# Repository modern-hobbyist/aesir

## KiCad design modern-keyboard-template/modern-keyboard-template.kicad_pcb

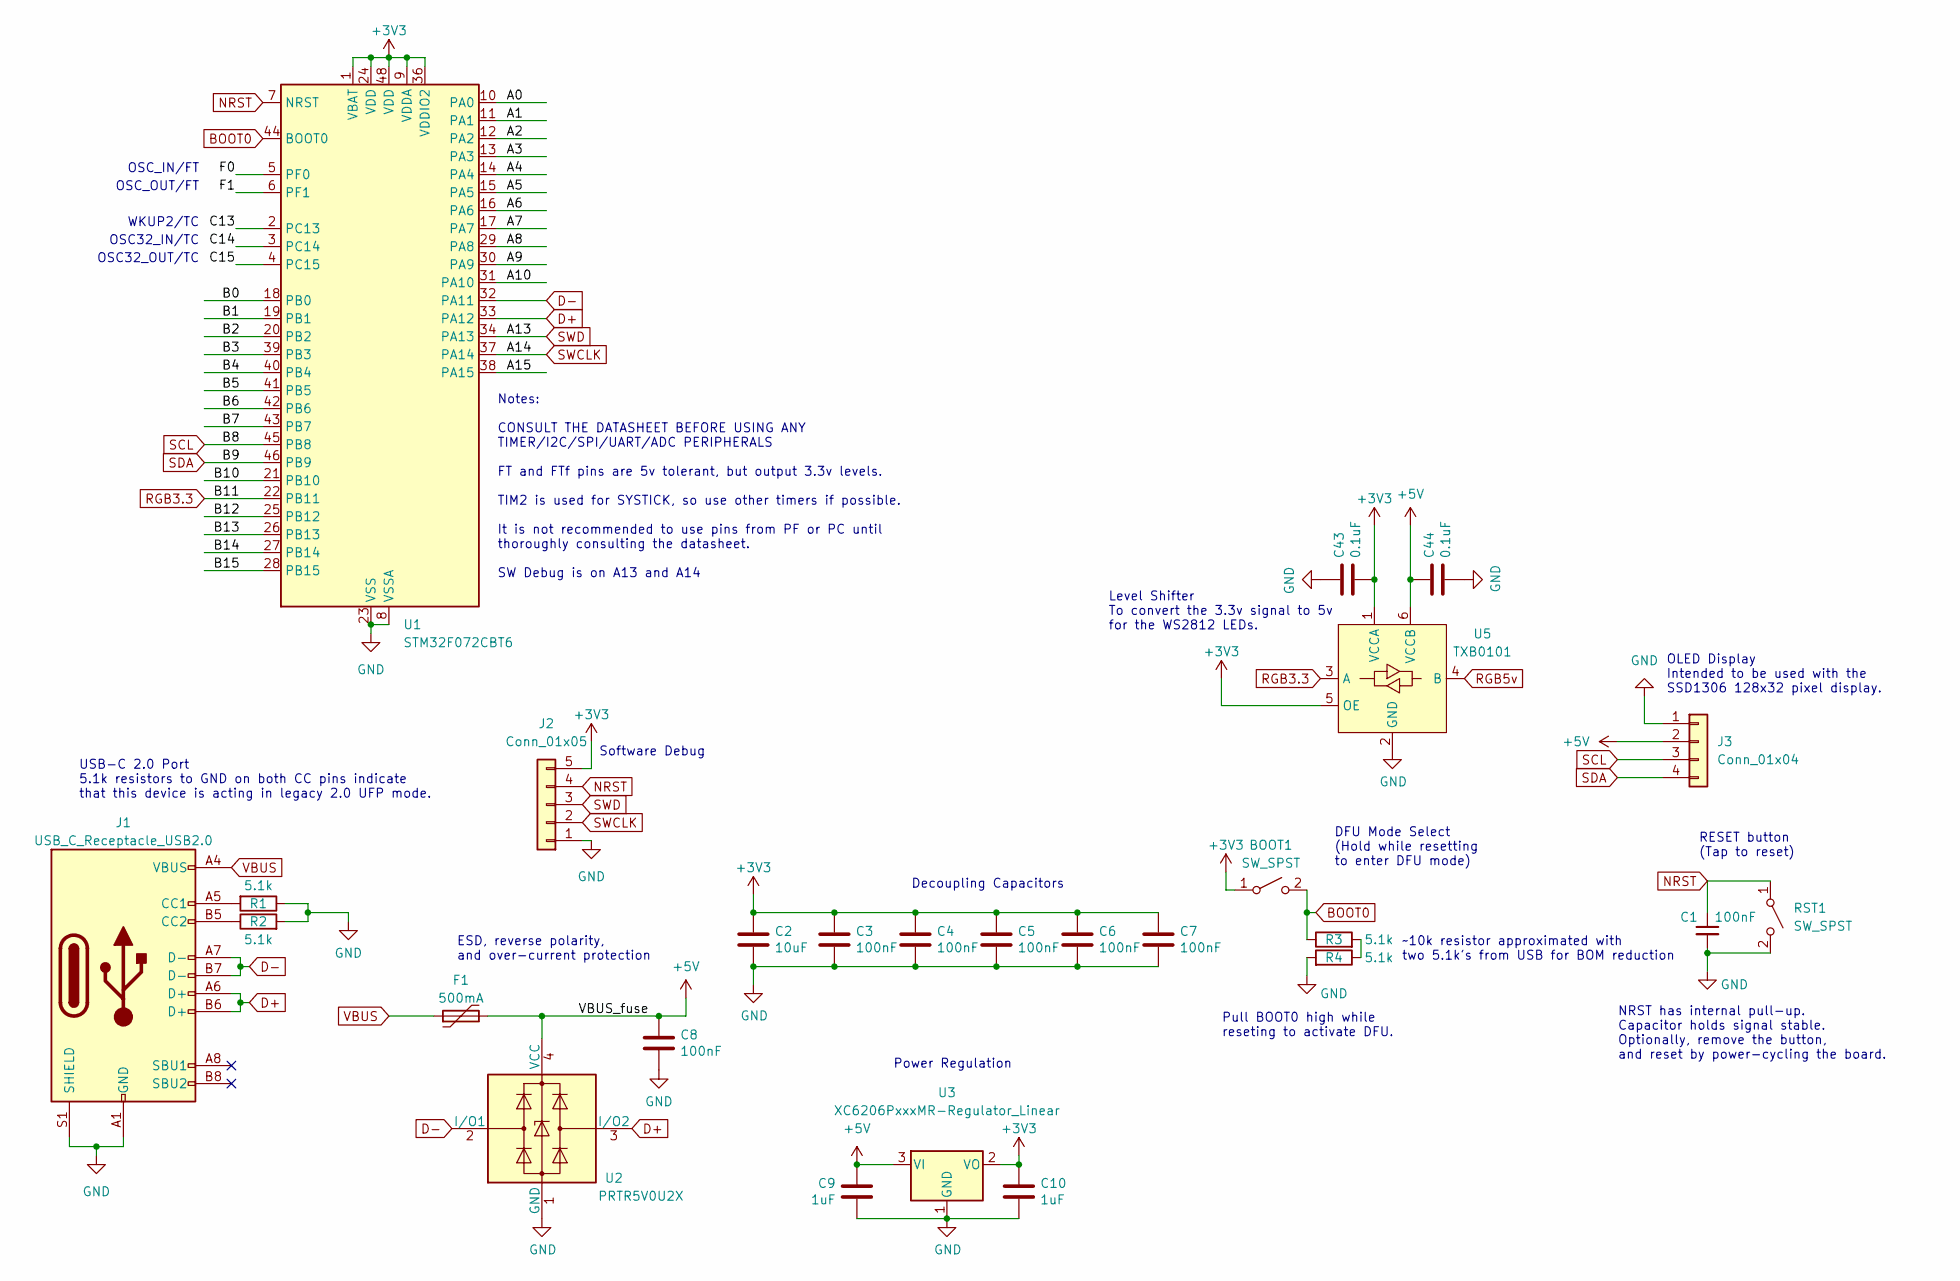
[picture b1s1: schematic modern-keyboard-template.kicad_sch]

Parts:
BOOT1: SW_SPST; SW_SPST_TL3342
C1, C3, C4, C5, C6, C7, C8: 100nF; C_0402_1005Metric; LCSC C307331
C2: 10uF; C_0603_1608Metric; LCSC C307331
C9, C10: 1uF; C_0402_1005Metric; LCSC C307331
C43, C44: 0.1uF; C_0402_1005Metric; LCSC C307331
F1: 500mA; Fuse_1206_3216Metric; LCSC C135341
J1: USB_C_Receptacle_USB2.0; USB_C_Receptacle_HRO_TYPE-C-31-M-12; JlcRotOffset 180
J2: Conn_01x05; PinHeader_1x05_P2.54mm_Vertical
J3: Conn_01x04; SSD1306-0.91-OLED-4pin-128x32
R1, R2, R3, R4: 5.1k; R_0402_1005Metric
RST1: SW_SPST; SW_SPST_TL3342
U1: STM32F072CBT6; LQFP-48_7x7mm_P0.5mm; JlcRotOffset 90
U2: PRTR5V0U2X; SOT-143; LCSC C2827688
U3: XC6206PxxxMR-Regulator_Linear; SOT-23; LCSC C5446
U5: TXB0101; SOT-363_SC-70-6_Handsoldering; LCSC C324081

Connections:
+3V3: BOOT1.1 (A), C2.1, C3.1, C4.1, C5.1, C6.1, C7.1, C10.1, C43.2, J2.5, U1.1 (VBAT), U1.9 (VDDA), U1.24 (VDD), U1.36 (VDDIO2), U1.48 (VDD), U3.2 (VO), U5.1 (VCCA), U5.5 (OE)
+5V: C8.1, C9.1, C44.1, F1.2, J3.2, U2.4 (VCC), U3.3 (VI), U5.6 (VCCB)
/A0: U1.10 (PA0)
/A1: U1.11 (PA1)
/A2: U1.12 (PA2)
/A3: U1.13 (PA3)
/A4: U1.14 (PA4)
/A5: U1.15 (PA5)
/A6: U1.16 (PA6)
/A7: U1.17 (PA7)
/A8: U1.29 (PA8)
/A9: U1.30 (PA9)
/A10: U1.31 (PA10)
/A15: U1.38 (PA15)
/B0: U1.18 (PB0)
/B1: U1.19 (PB1)
/B2: U1.20 (PB2)
/B3: U1.39 (PB3)
/B4: U1.40 (PB4)
/B5: U1.41 (PB5)
/B6: U1.42 (PB6)
/B7: U1.43 (PB7)
/B10: U1.21 (PB10)
/B12: U1.25 (PB12)
/B13: U1.26 (PB13)
/B14: U1.27 (PB14)
/B15: U1.28 (PB15)
/C13: U1.2 (PC13)
/C14: U1.3 (PC14)
/C15: U1.4 (PC15)
/F0: U1.5 (PF0)
/F1: U1.6 (PF1)
BOOT0: BOOT1.2 (B), R3.1, U1.44 (BOOT0)
D+: J1.A6 (D+), J1.B6 (D+), U1.33 (PA12), U2.3 (I/O2)
D-: J1.A7 (D-), J1.B7 (D-), U1.32 (PA11), U2.2 (I/O1)
GND: C1.2, C2.2, C3.2, C4.2, C5.2, C6.2, C7.2, C8.2, C9.2, C10.2, C43.1, C44.2, J1.A1 (GND), J1.A12 (GND), J1.B1 (GND), J1.B12 (GND), J1.S1 (SHIELD), J2.1, J3.1, R1.1, R2.2, R4.2, RST1.2 (B), U1.8 (VSSA), U1.23 (VSS), U1.35 (VSS), U1.47 (VSS), U2.1 (GND), U3.1 (GND), U5.2 (GND)
NRST: C1.1, J2.4, RST1.1 (A), U1.7 (NRST)
unnamed: J1.A5 (CC1), R1.2
unnamed: J1.B5 (CC2), R2.1
unnamed: R3.2, R4.1
RGB3.3: U1.22 (PB11), U5.3 (A)
RGB5v: U5.4 (B)
SCL: J3.3, U1.45 (PB8)
SDA: J3.4, U1.46 (PB9)
SWCLK: J2.2, U1.37 (PA14)
SWD: J2.3, U1.34 (PA13)
VBUS: F1.1, J1.A4 (VBUS), J1.A9 (VBUS), J1.B4 (VBUS), J1.B9 (VBUS)

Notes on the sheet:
Decoupling Capacitors
~10k resistor approximated with two 5.1k's from USB for BOM reduction
Notes: CONSULT THE DATASHEET BEFORE USING ANY TIMER/I2C/SPI/UART/ADC PERIPHERALS FT and FTf pins are 5v tolerant, but output 3.3v levels. TIM2 is used for SYSTICK, so use other timers if possible. It is not recommended to use pins from PF or PC until thoroughly consulting the datasheet. SW Debug is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
RESET button (Tap to reset)
Power Regulation
OSC_IN/FT
OLED Display Intended to be used with the SSD1306 128x32 pixel display.
OSC32_OUT/TC
USB-C 2.0 Port 5.1k resistors to GND on both CC pins indicate that this device is acting in legacy 2.0 UFP mode.
WKUP2/TC
OSC_OUT/FT
ESD, reverse polarity, and over-current protection
Software Debug
NRST has internal pull-up. Capacitor holds signal stable. Optionally, remove the button, and reset by power-cycling the board.
OSC32_IN/TC
Pull BOOT0 high while reseting to activate DFU.
Level Shifter To convert the 3.3v signal to 5v for the WS2812 LEDs.
DFU Mode Select (Hold while resetting to enter DFU mode)

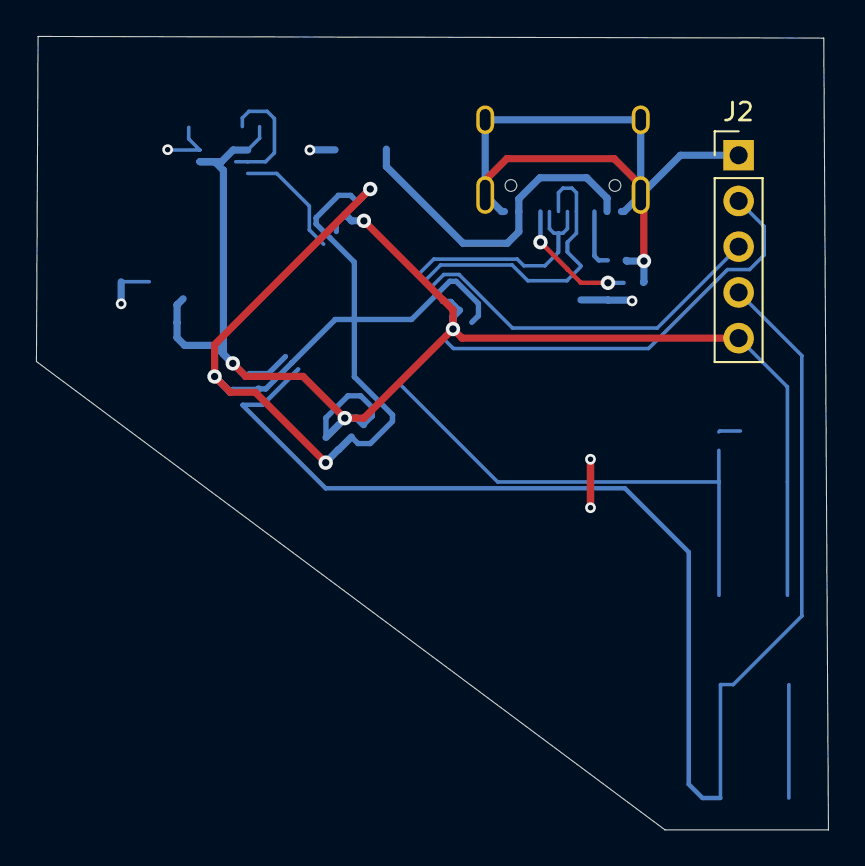
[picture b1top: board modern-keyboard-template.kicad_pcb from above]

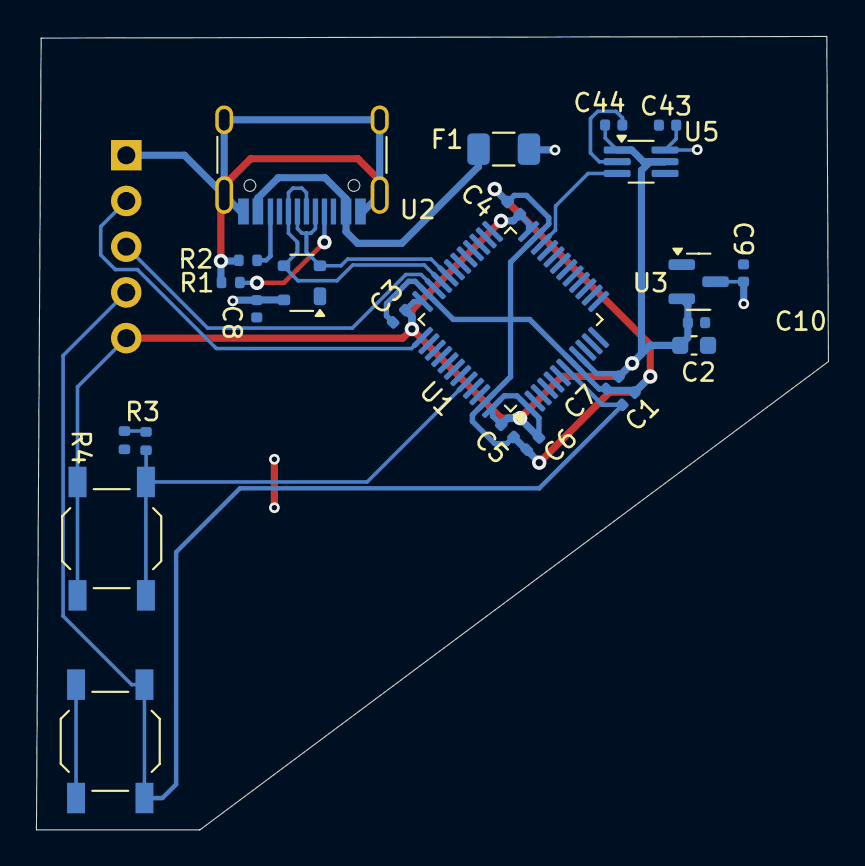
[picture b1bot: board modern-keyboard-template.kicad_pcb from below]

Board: 2 copper layers, 44.0 x 44.1 mm, 25 parts (24 on the bottom side), 14 nets.

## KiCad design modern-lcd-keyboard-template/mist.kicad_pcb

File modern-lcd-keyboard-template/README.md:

# Modern LCD Keyboard Template

> **Note:** This PCB is untested. I made updates to this design to address issues I had with the previous version, but I haven't ordered boards, nor have I written the matching firmware for it.

This is a starter template for a Keyboard PCB to help you get started quickly with the right footprints and supplemental components to get it done right.

## Features
- TBD

## Specifications

- **Microcontroller**: STM32G474CETx
- **Key Layout**: Split layout with additional keys for layers and macros.
- **Display**: 2.2" LCD (320x240 resolution) per half.
- **Lighting**: SK6812 Mini RGB LEDs.
- **Switches**: Kailh Choc Low Profile.

## License

This project is licensed under the MIT License. See the [LICENSE](../LICENSE) file for details.

## Acknowledgments

- The QMK community for their amazing firmware.
- Adafruit for the GFX library support.
- Inspiration from the mechanical keyboard enthusiast community.

---

For more information, check out the [Modern Hobbyist YouTube channel](https://www.youtube.com/ModernHobbyist) for videos about this project!

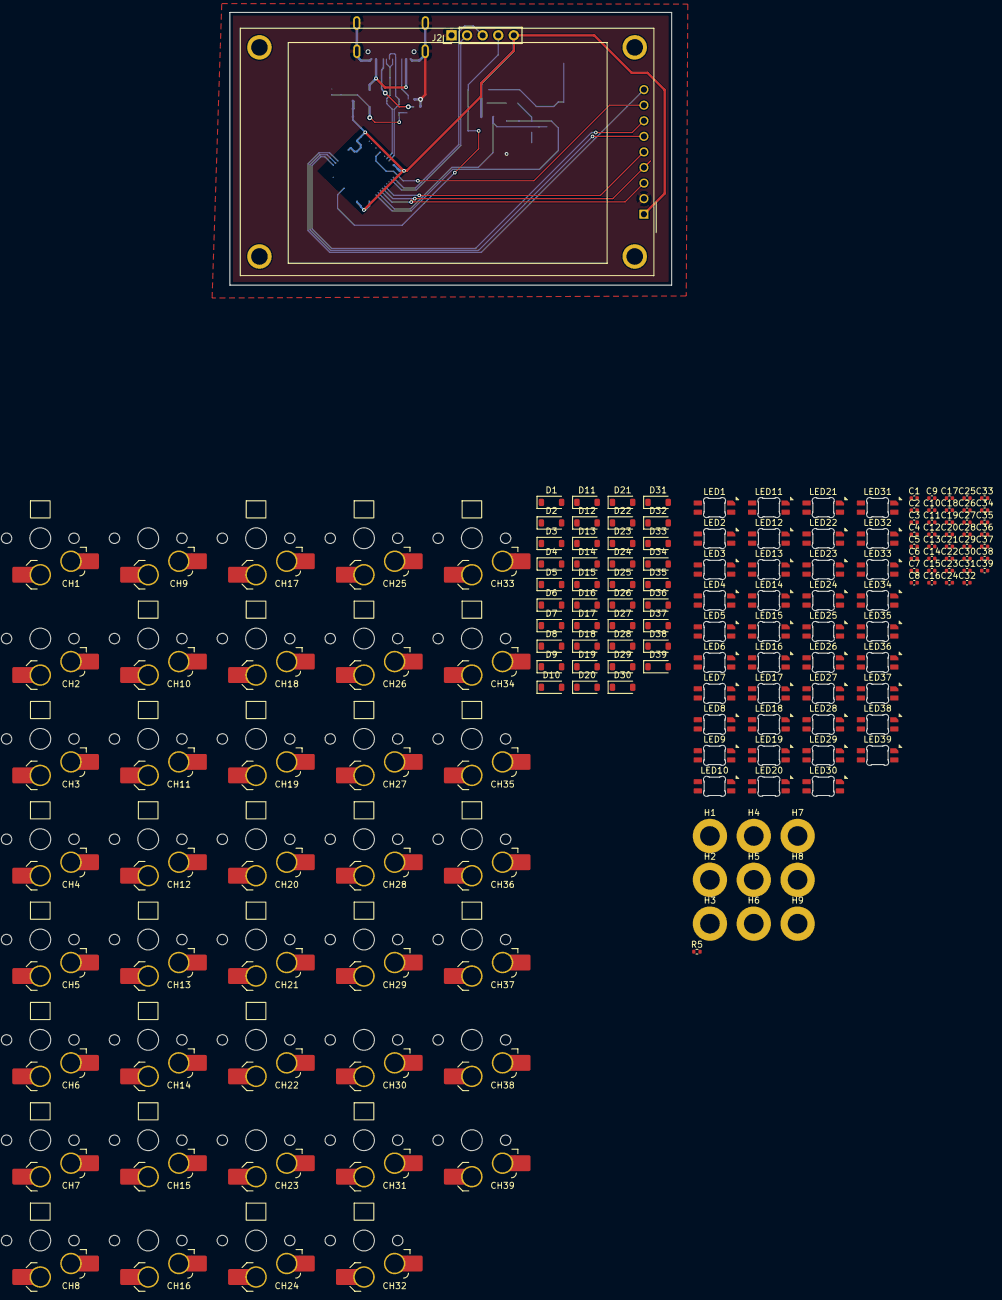
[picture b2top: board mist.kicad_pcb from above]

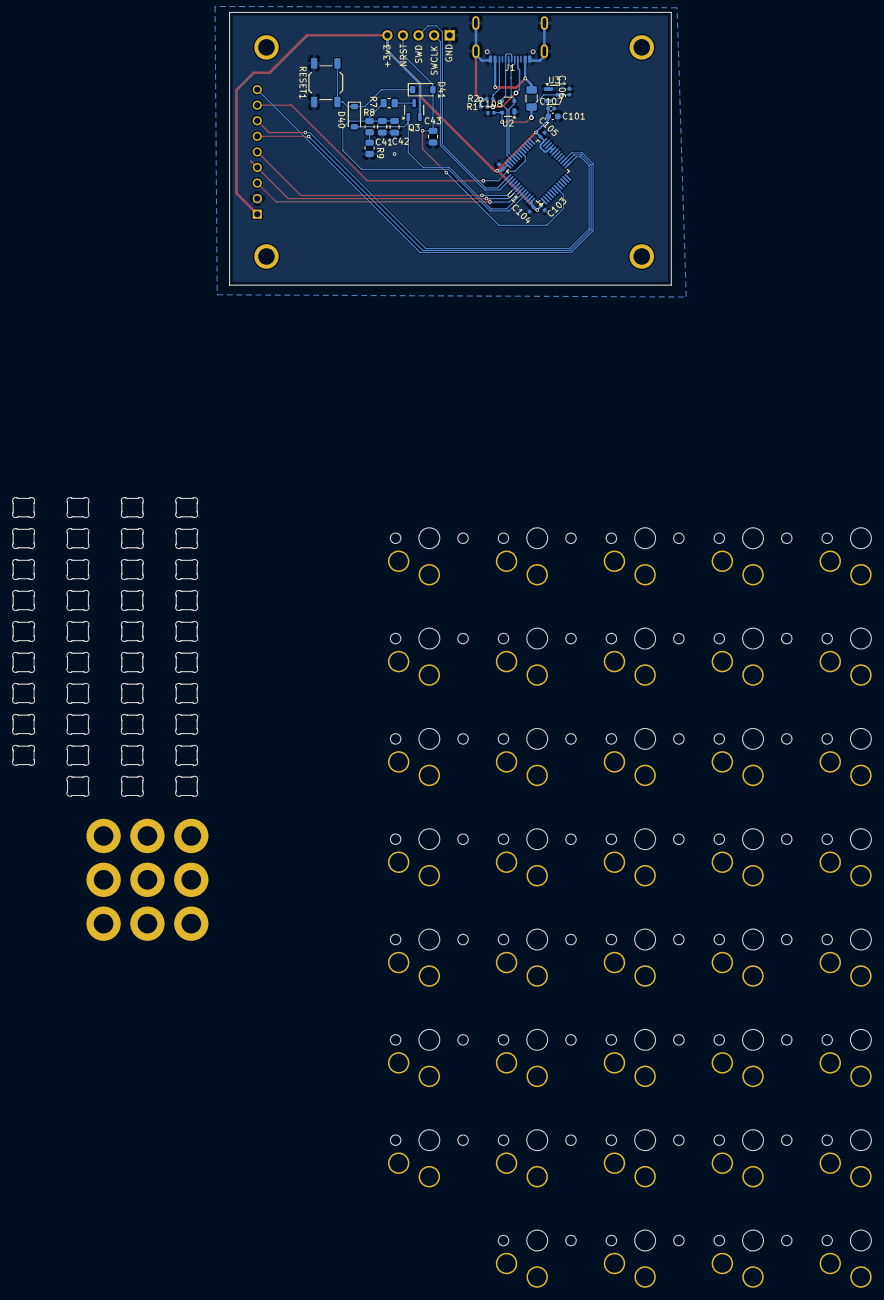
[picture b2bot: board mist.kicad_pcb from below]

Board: 2 copper layers, 193 parts (25 on the bottom side), 114 nets.

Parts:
C1, C2, C3, C4, C5, C6, C7, C8, C9, C10, C11, C12, C13, C14, C15, C16, C17, C18, C19, C20, C21, C22, C23, C24, C25, C26, C27, C28, C29, C30, C31, C32, C33, C34, C35, C36, C37, C38, C39: 0.1uF; C_0402_1005Metric
C41, C42, C43: 100n; C_0805_2012Metric
C101: 10uF; C_0603_1608Metric
C102, C103, C104, C105, C108: 100nF; C_0402_1005Metric
C106, C107: 1uF; C_0402_1005Metric
CH1, CH3, CH4, CH5, CH6, CH7, CH8, CH10, CH11, CH12, CH13, CH14, CH15, CH17, CH18, CH19, CH20, CH21, CH22, CH24, CH25, CH26, CH27, CH28, CH29, CH31, CH32, CH33, CH34, CH35, CH36, CH37: choc_v1_SW_HS; SW_choc_v1_HS_CPG135001S30_1u
CH2, CH9, CH16, CH23, CH30, CH38, CH39: choc_v1_SW_HS; SW_choc_v1_HS_CPG135001S30_1.5u
D1, D2, D3, D4, D5, D6, D7, D8, D9, D10, D11, D12, D13, D14, D15, D16, D17, D18, D19, D20, D21, D22, D23, D24, D25, D26, D27, D28, D29, D30, D31, D32, D33, D34, D35, D36, D37, D38, D39: D; D_SOD-123
D40, D41: 1N4148; D_SOD-123
F1: 500mA; Fuse_1206_3216Metric
H1, H2, H3, H4, H5, H6, H7, H8, H9: MountingHole_Pad; MountingHole_3.2mm_M3_DIN965_Pad
J1: USB_C_Receptacle_USB2.0; USB_C_Receptacle_HRO_TYPE-C-31-M-14
J2: Conn_01x05; PinHeader_1x05_P2.54mm_Vertical
LED1, LED2, LED3, LED4, LED5, LED6, LED7, LED8, LED9, LED10, LED11, LED12, LED13, LED14, LED15, LED16, LED17, LED18, LED19, LED20, LED21, LED22, LED23, LED24, LED25, LED26, LED27, LED28, LED29, LED30, LED31, LED32, LED33, LED34, LED35, LED36, LED37, LED38, LED39: choc_SK6812MINI-E; LED_choc_6028R
Q3: MMUN2133LT1G; SOT-23-3
R1, R2, R5: 5.1k; R_0402_1005Metric
R7: 120; R_0805_2012Metric
R8, R9: 68k; R_0805_2012Metric
RESET1: DFU; SW_SPST_TL3342
U1: STM32G474CETx; LQFP-48_7x7mm_P0.5mm
U2: PRTR5V0U2X; SOT-143
U3: XC6206PxxxMR-Regulator_Linear; SOT-23
U4: CR2013-MI2120

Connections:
+3V3: C101.1, C102.1, C103.1, C104.1, C105.1, C107.1, J2.5, Q3.2 (E), U1.1 (VBAT), U1.20 (VREF+), U1.21 (VDDA), U1.24 (VDD), U1.36 (VDD), U1.48 (VDD), U3.2 (VO), U4.1 (VCC)
+5V: C1.1, C2.1, C3.1, C4.1, C5.1, C6.1, C7.1, C8.1, C9.1, C10.1, C11.1, C12.1, C13.1, C14.1, C15.1, C16.1, C17.1, C18.1, C19.1, C20.1, C21.1, C22.1, C23.1, C24.1, C25.1, C26.1, C27.1, C28.1, C29.1, C30.1, C31.1, C32.1, C33.1, C34.1, C35.1, C36.1, C37.1, C38.1, C39.1, C106.1, C108.1, F1.2, LED1.1 (VDD), LED2.1 (VDD), LED3.1 (VDD), LED4.1 (VDD), LED5.1 (VDD), LED6.1 (VDD), LED7.1 (VDD), LED8.1 (VDD), LED9.1 (VDD), LED10.1 (VDD), LED11.1 (VDD), LED12.1 (VDD), LED13.1 (VDD), LED14.1 (VDD), LED15.1 (VDD), LED16.1 (VDD), LED17.1 (VDD), LED18.1 (VDD), LED19.1 (VDD), LED20.1 (VDD), LED21.1 (VDD), LED22.1 (VDD), LED23.1 (VDD), LED24.1 (VDD), LED25.1 (VDD), LED26.1 (VDD), LED27.1 (VDD), LED28.1 (VDD), LED29.1 (VDD), LED30.1 (VDD), LED31.1 (VDD), LED32.1 (VDD), LED33.1 (VDD), LED34.1 (VDD), LED35.1 (VDD), LED36.1 (VDD), LED37.1 (VDD), LED38.1 (VDD), LED39.1 (VDD), R5.1, U2.4 (VCC), U3.3 (VI)
BOOT0: C41.2, C42.2, R7.2, R8.2, U1.45 (PB8)
BOOT0_CHRG: D40.2 (A), Q3.1 (B), U1.44 (PB7)
D+: J1.A6 (D+), J1.B6 (D+), U1.34 (PA12), U2.3 (I/O2)
D-: J1.A7 (D-), J1.B7 (D-), U1.33 (PA11), U2.2 (I/O1)
DOut1: LED1.2 (DOUT), LED8.3 (DIN)
DOut2: LED14.2 (DOUT), LED21.3 (DIN)
DOut3: LED15.2 (DOUT), LED22.3 (DIN)
DOut4: LED28.2 (DOUT), LED35.3 (DIN)
DOut5: LED29.2 (DOUT), LED36.3 (DIN)
GND: C1.2, C2.2, C3.2, C4.2, C5.2, C6.2, C7.2, C8.2, C9.2, C10.2, C11.2, C12.2, C13.2, C14.2, C15.2, C16.2, C17.2, C18.2, C19.2, C20.2, C21.2, C22.2, C23.2, C24.2, C25.2, C26.2, C27.2, C28.2, C29.2, C30.2, C31.2, C32.2, C33.2, C34.2, C35.2, C36.2, C37.2, C38.2, C39.2, C41.1, C42.1, C43.1, C101.2, C102.2, C103.2, C104.2, C105.2, C106.2, C107.2, C108.2, H1.1, H2.1, H3.1, H4.1, H5.1, H6.1, H7.1, H8.1, H9.1, J1.A1 (GND), J1.A12 (GND), J1.B1 (GND), J1.B12 (GND), J1.S1 (SHIELD), J2.1, LED1.4 (VSS), LED2.4 (VSS), LED3.4 (VSS), LED4.4 (VSS), LED5.4 (VSS), LED6.4 (VSS), LED7.4 (VSS), LED8.4 (VSS), LED9.4 (VSS), LED10.4 (VSS), LED11.4 (VSS), LED12.4 (VSS), LED13.4 (VSS), LED14.4 (VSS), LED15.4 (VSS), LED16.4 (VSS), LED17.4 (VSS), LED18.4 (VSS), LED19.4 (VSS), LED20.4 (VSS), LED21.4 (VSS), LED22.4 (VSS), LED23.4 (VSS), LED24.4 (VSS), LED25.4 (VSS), LED26.4 (VSS), LED27.4 (VSS), LED28.4 (VSS), LED29.4 (VSS), LED30.4 (VSS), LED31.4 (VSS), LED32.4 (VSS), LED33.4 (VSS), LED34.4 (VSS), LED35.4 (VSS), LED36.4 (VSS), LED37.4 (VSS), LED38.4 (VSS), LED39.4 (VSS), R1.1, R2.2, R9.2, RESET1.1, U1.19 (VSSA), U1.23 (VSS), U1.35 (VSS), U1.47 (VSS), U2.1 (GND), U3.1 (GND), U4.2 (GND)
LCD_BL_PWM: U1.30 (PA8), U4.8 (LED)
LCD_CS: U1.43 (PB6), U4.3 (~CS)
LCD_DC: U1.41 (PB4), U4.5 (D/~C)
LCD_MISO: U1.15 (PA7), U4.9 (MISO)
LCD_MOSI: U1.14 (PA6), U4.6 (MOSI)
LCD_RST: U1.42 (PB5), U4.4 (RESET)
LCD_SCK: U1.13 (PA5), U4.7 (SCK)
NRST: C43.2, D41.2 (A), J2.4, U1.7 (PG10)
unnamed: CH1.2, D1.2 (A)
unnamed: CH2.2, D2.2 (A)
unnamed: CH3.2, D3.2 (A)
unnamed: CH4.2, D4.2 (A)
unnamed: CH5.2, D5.2 (A)
unnamed: CH6.2, D6.2 (A)
unnamed: CH7.2, D7.2 (A)
unnamed: CH8.2, D8.2 (A)
unnamed: CH9.2, D9.2 (A)
unnamed: CH10.2, D10.2 (A)
unnamed: CH11.2, D11.2 (A)
unnamed: CH12.2, D12.2 (A)
unnamed: CH13.2, D13.2 (A)
unnamed: CH14.2, D14.2 (A)
unnamed: CH15.2, D15.2 (A)
unnamed: CH16.2, D16.2 (A)
unnamed: CH17.2, D17.2 (A)
unnamed: CH18.2, D18.2 (A)
unnamed: CH19.2, D19.2 (A)
unnamed: CH20.2, D20.2 (A)
unnamed: CH21.2, D21.2 (A)
unnamed: CH22.2, D22.2 (A)
unnamed: CH23.2, D23.2 (A)
unnamed: CH24.2, D24.2 (A)
unnamed: CH25.2, D25.2 (A)
unnamed: CH26.2, D26.2 (A)
unnamed: CH27.2, D27.2 (A)
unnamed: CH28.2, D28.2 (A)
unnamed: CH29.2, D29.2 (A)
unnamed: CH30.2, D30.2 (A)
unnamed: CH31.2, D31.2 (A)
unnamed: CH32.2, D32.2 (A)
unnamed: CH33.2, D33.2 (A)
unnamed: CH34.2, D34.2 (A)
unnamed: CH35.2, D35.2 (A)
unnamed: CH36.2, D36.2 (A)
unnamed: CH37.2, D37.2 (A)
unnamed: CH38.2, D38.2 (A)
unnamed: CH39.2, D39.2 (A)
unnamed: D40.1 (K), D41.1 (K), RESET1.2
unnamed: J1.A5 (CC1), R1.2
unnamed: J1.B5 (CC2), R2.1
unnamed: LED1.3 (DIN), LED2.2 (DOUT)
unnamed: LED2.3 (DIN), LED3.2 (DOUT)
unnamed: LED3.3 (DIN), LED4.2 (DOUT)
unnamed: LED4.3 (DIN), LED5.2 (DOUT)
unnamed: LED5.3 (DIN), LED6.2 (DOUT)
unnamed: LED6.3 (DIN), LED7.2 (DOUT)
unnamed: LED8.2 (DOUT), LED9.3 (DIN)
unnamed: LED9.2 (DOUT), LED10.3 (DIN)
unnamed: LED10.2 (DOUT), LED11.3 (DIN)
unnamed: LED11.2 (DOUT), LED12.3 (DIN)
unnamed: LED12.2 (DOUT), LED13.3 (DIN)
unnamed: LED13.2 (DOUT), LED14.3 (DIN)
unnamed: LED15.3 (DIN), LED16.2 (DOUT)
unnamed: LED16.3 (DIN), LED17.2 (DOUT)
unnamed: LED17.3 (DIN), LED18.2 (DOUT)
unnamed: LED18.3 (DIN), LED19.2 (DOUT)
unnamed: LED19.3 (DIN), LED20.2 (DOUT)
unnamed: LED20.3 (DIN), LED21.2 (DOUT)
unnamed: LED22.2 (DOUT), LED23.3 (DIN)
unnamed: LED23.2 (DOUT), LED24.3 (DIN)
unnamed: LED24.2 (DOUT), LED25.3 (DIN)
unnamed: LED25.2 (DOUT), LED26.3 (DIN)
unnamed: LED26.2 (DOUT), LED27.3 (DIN)
unnamed: LED27.2 (DOUT), LED28.3 (DIN)
unnamed: LED29.3 (DIN), LED30.2 (DOUT)
unnamed: LED30.3 (DIN), LED31.2 (DOUT)
unnamed: LED31.3 (DIN), LED32.2 (DOUT)
unnamed: LED32.3 (DIN), LED33.2 (DOUT)
unnamed: LED33.3 (DIN), LED34.2 (DOUT)
unnamed: LED34.3 (DIN), LED35.2 (DOUT)
unnamed: LED36.2 (DOUT), LED37.3 (DIN)
unnamed: LED37.2 (DOUT), LED38.3 (DIN)
unnamed: LED38.2 (DOUT), LED39.3 (DIN)
unnamed: Q3.3 (C), R7.1
unnamed: R8.1, R9.1
RGB5v: LED7.3 (DIN), R5.2, U1.39 (PA15)
SWCLK: J2.2, U1.38 (PA14)
SWD: J2.3, U1.37 (PA13)
VBUS: F1.1, J1.A4 (VBUS), J1.A9 (VBUS), J1.B4 (VBUS), J1.B9 (VBUS)
col0: CH1.1, CH8.1, CH15.1, CH22.1, CH29.1, U1.4 (PC15)
col1: CH2.1, CH9.1, CH16.1, CH23.1, CH30.1, U1.3 (PC14)
col2: CH3.1, CH10.1, CH17.1, CH24.1, CH31.1, U1.28 (PB14)
col3: CH4.1, CH11.1, CH18.1, CH25.1, CH32.1, CH36.1, U1.29 (PB15)
col4: CH5.1, CH12.1, CH19.1, CH26.1, CH33.1, CH37.1, U1.18 (PB2)
col5: CH6.1, CH13.1, CH20.1, CH27.1, CH34.1, CH38.1, U1.17 (PB1)
col6: CH7.1, CH14.1, CH21.1, CH28.1, CH35.1, CH39.1, U1.2 (PC13)
row0: D1.1 (K), D2.1 (K), D3.1 (K), D4.1 (K), D5.1 (K), D6.1 (K), D7.1 (K), U1.22 (PB10)
row1: D8.1 (K), D9.1 (K), D10.1 (K), D11.1 (K), D12.1 (K), D13.1 (K), D14.1 (K), U1.40 (PB3)
row2: D15.1 (K), D16.1 (K), D17.1 (K), D18.1 (K), D19.1 (K), D20.1 (K), D21.1 (K), U1.26 (PB12)
row3: D22.1 (K), D23.1 (K), D24.1 (K), D25.1 (K), D26.1 (K), D27.1 (K), D28.1 (K), U1.27 (PB13)
row4: D29.1 (K), D30.1 (K), D31.1 (K), D32.1 (K), D33.1 (K), D34.1 (K), D35.1 (K), U1.16 (PB0)
row5: D36.1 (K), D37.1 (K), D38.1 (K), D39.1 (K), U1.12 (PA4)
